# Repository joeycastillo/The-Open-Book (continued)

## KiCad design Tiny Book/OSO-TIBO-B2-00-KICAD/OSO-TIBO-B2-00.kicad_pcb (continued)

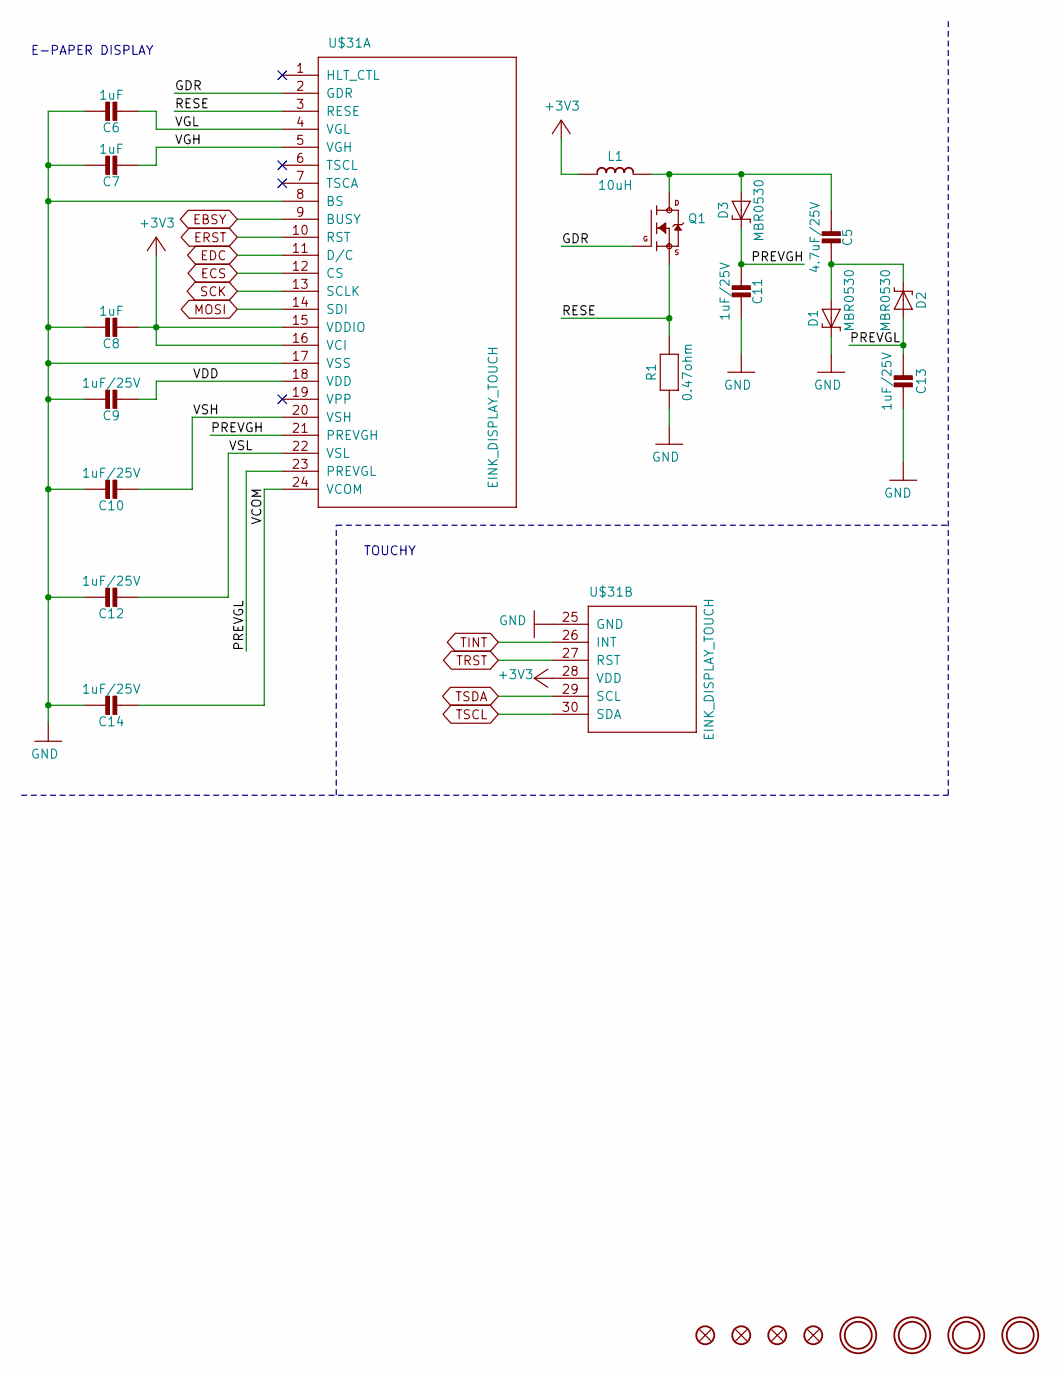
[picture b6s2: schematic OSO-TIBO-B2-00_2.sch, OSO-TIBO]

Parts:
C5: 4.7uF/25V; 0805-NO
C6, C7, C8: 1uF; 0805_10MGAP
C9, C10, C11, C12, C13, C14: 1uF/25V; 0805_10MGAP
D1, D2, D3: MBR0530; SOD-123
FID1, FID2, FID3, FID4: FIDUCIAL_1MM
L1: 10uH; MICROBUILDER_INDUCTOR_4X4MM_NR401_BIGPADS
Q1: IRLML0100; SOT23-3
R1: 0.47ohm; 0805_10MGAP
U$1, U$4, U$5, U$7: MOUNTINGHOLE2.5; MOUNTINGHOLE_2.5_PLATED
U$31: EINK_DISPLAY_TOUCH; EINK_DISPLAY_2_7_IN_TOUCH

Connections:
+3V3: C8.2, L1.P$1 (1), U$31.15 (VDDIO), U$31.16 (VCI), U$31.28 (VDD); also elsewhere on the board
/OSO-TIBO-B2-00_2/GDR: Q1.1 (G), U$31.2 (GDR)
/OSO-TIBO-B2-00_2/PREVGH: C11.1, D3.C, U$31.21 (PREVGH)
/OSO-TIBO-B2-00_2/PREVGL: C13.1, D2.A, U$31.23 (PREVGL)
/OSO-TIBO-B2-00_2/RESE: Q1.2 (S), R1.1, U$31.3 (RESE)
/OSO-TIBO-B2-00_2/VCOM: C14.2, U$31.24 (VCOM)
/OSO-TIBO-B2-00_2/VDD: C9.2, U$31.18 (VDD)
/OSO-TIBO-B2-00_2/VGH: C7.2, U$31.5 (VGH)
/OSO-TIBO-B2-00_2/VGL: C6.2, U$31.4 (VGL)
/OSO-TIBO-B2-00_2/VSH: C10.2, U$31.20 (VSH)
/OSO-TIBO-B2-00_2/VSL: C12.2, U$31.22 (VSL)
EBSY: U$31.9 (BUSY); also elsewhere on the board
ECS: U$31.12 (CS); also elsewhere on the board
EDC: U$31.11 (D/C); also elsewhere on the board
ERST: U$31.10 (RST); also elsewhere on the board
GND: C6.1, C7.1, C8.1, C9.1, C10.1, C11.2, C12.1, C13.2, C14.1, D1.C, R1.2, U$31.8 (BS), U$31.17 (VSS), U$31.25 (GND); also elsewhere on the board
MOSI: U$31.14 (SDI); also elsewhere on the board
unnamed: C5.1, D3.A, L1.P$2 (2), Q1.3 (D)
unnamed: C5.2, D1.A, D2.C
SCK: U$31.13 (SCLK); also elsewhere on the board
TINT: U$31.26 (INT); also elsewhere on the board
TRST: U$31.27 (RST); also elsewhere on the board
TSCL: U$31.30 (SDA); also elsewhere on the board
TSDA: U$31.29 (SCL); also elsewhere on the board

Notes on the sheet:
E-PAPER DISPLAY
TOUCHY

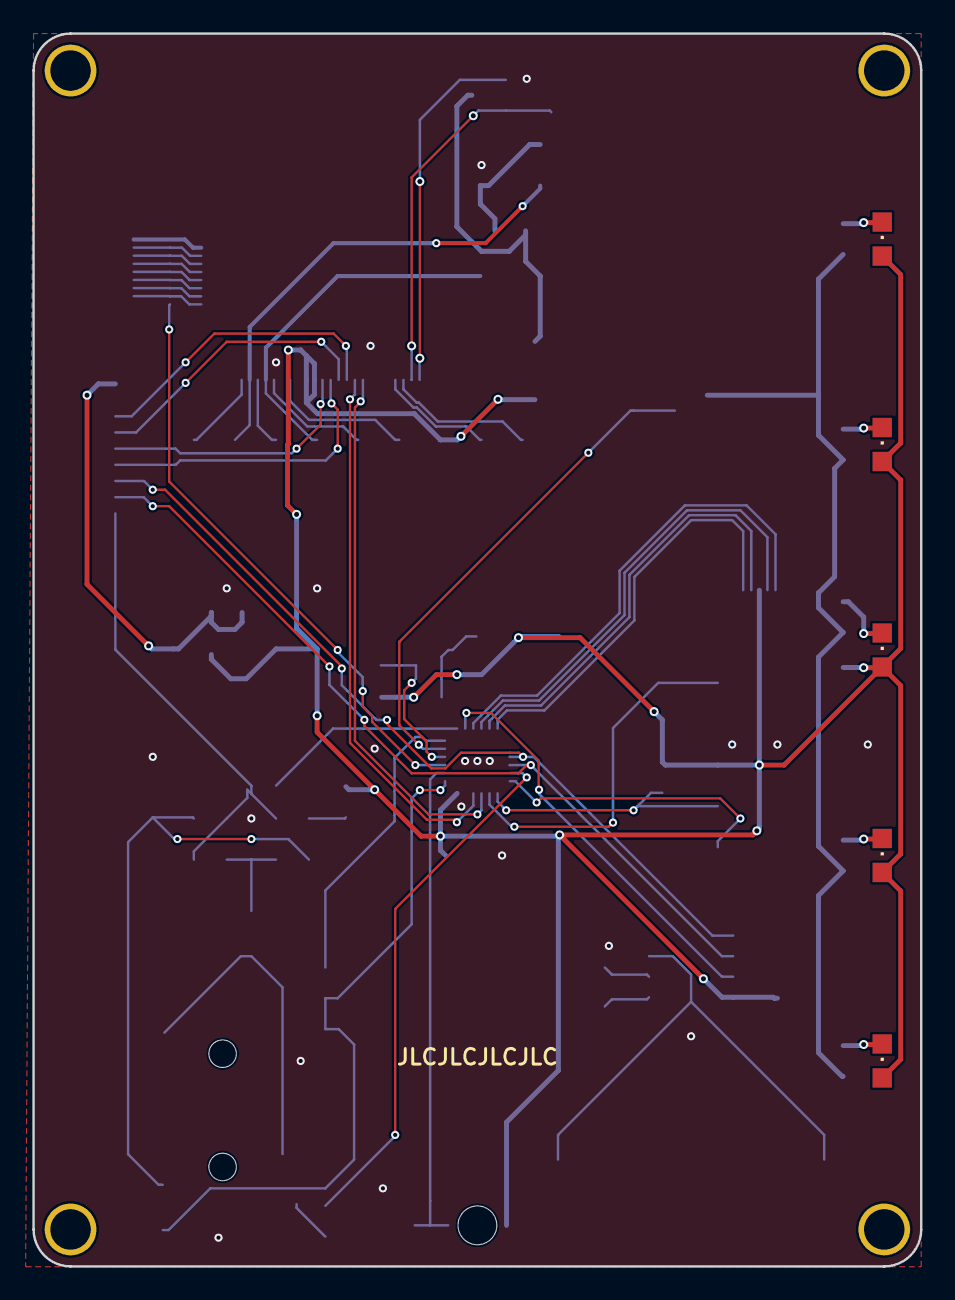
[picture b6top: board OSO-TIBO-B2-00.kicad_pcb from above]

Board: 2 copper layers, 54.9 x 76.2 mm, 78 parts (0 on the bottom side), 62 nets.

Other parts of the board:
LED6: BLU; CHIPLED_0805
U$37: OSO_WORDMARK_THREELINE_450MIL_1000DPI
U$44: OSO_BEAR_250X360MIL_1000DPI

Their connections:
GND: LED6.C; also elsewhere on the board
unnamed 52: LED6.A; also elsewhere on the board

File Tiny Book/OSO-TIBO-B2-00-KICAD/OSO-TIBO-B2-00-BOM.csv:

Reference, Quantity, Value, Footprint, Datasheet
B1 ,1,"CR1220","OSO-TIBO-B2-00:CR1220",""
C1 C17 C2 ,3,"10µF","OSO-TIBO-B2-00:0805-NO",""
C10 C11 C12 C13 C14 C9 ,6,"1uF/25V","OSO-TIBO-B2-00:0805_10MGAP",""
C16 ,1,"100uF","OSO-TIBO-B2-00:C1210",""
C15 C18 C3 ,3,"1uF","OSO-TIBO-B2-00:0805-NO",""
C5 ,1,"4.7uF/25V","OSO-TIBO-B2-00:0805-NO",""
C6 C7 C8 ,3,"1uF","OSO-TIBO-B2-00:0805_10MGAP",""
D1 D2 D3 ,3,"MBR0530","OSO-TIBO-B2-00:SOD-123",""
D6 ,1,"1N4148","OSO-TIBO-B2-00:SOD-123",""
FB1 FB2 ,2,"Ferrite","OSO-TIBO-B2-00:0805",""
FID1 FID2 FID3 FID4 ,4,"FIDUCIAL_1MM","OSO-TIBO-B2-00:FIDUCIAL_1MM",""
J1 ,1,"HEADER-1X9_JSTSH","OSO-TIBO-B2-00:JST_SH9",""
J2 ,1,"SJ-43514-SMT","OSO-TIBO-B2-00:CUI_SJ-43514-SMT",""
J3 ,1,"52746-8","OSO-TIBO-B2-00:52746-8",""
L1 ,1,"10uH","OSO-TIBO-B2-00:MICROBUILDER_INDUCTOR_4X4MM_NR401_BIGPADS",""
LED1 LED2 LED3 LED4 LED5 ,5,"WHITE","OSO-TIBO-B2-00:CHIPLED_0805",""
LED6 ,1,"BLU","OSO-TIBO-B2-00:CHIPLED_0805",""
Q1 ,1,"IRLML0100","OSO-TIBO-B2-00:SOT23-3",""
Q2 ,1,"DMG3406","OSO-TIBO-B2-00:SOT23-WIDE",""
Q3 ,1,"BSS138","OSO-TIBO-B2-00:SOT23-WIDE",""
R1 ,1,"0.47ohm","OSO-TIBO-B2-00:0805_10MGAP",""
R11 ,1,"10K","OSO-TIBO-B2-00:EXB2HV",""
R13 R14 R15 R16 R17 ,5,"10Ω","OSO-TIBO-B2-00:0805-NO",""
R10 R12 R18 R2 R4 R9 ,6,"10K","OSO-TIBO-B2-00:0805-NO",""
R3 ,1,"100~~220 (TBD)","OSO-TIBO-B2-00:0805-NO",""
R5 R6 ,2,"10K","OSO-TIBO-B2-00:_0805MP",""
R7 R8 ,2,"100","OSO-TIBO-B2-00:_0805MP",""
SJ1 ,1,"SOLDERJUMPERREFLOW_NOPASTE","OSO-TIBO-B2-00:SOLDERJUMPER_REFLOW_NOPASTE",""
SP2 ,1,"7.5mm SPK","OSO-TIBO-B2-00:BUZZER_SMT_5MM",""
TP1 TP2 TP3 TP4 TP5 ,5,"TESTPOINTROUND2MMNO","OSO-TIBO-B2-00:TESTPOINT_ROUND_2MM_NO",""
U$1 U$4 U$5 U$7 ,4,"MOUNTINGHOLE2.5","OSO-TIBO-B2-00:MOUNTINGHOLE_2.5_PLATED",""
U$31 ,1,"EINK_DISPLAY_TOUCH","OSO-TIBO-B2-00:EINK_DISPLAY_2_7_IN_TOUCH",""
U1 ,1,"AP2112-3.3","OSO-TIBO-B2-00:SOT23-5",""
U2 ,1,"ATSAMD09D14A-MU","OSO-TIBO-B2-00:QFN24_4MM",""
U3 ,1,"ALS-PT21","OSO-TIBO-B2-00:ALS-PT26-21C",""
U4 ,1,"PCF8523T","OSO-TIBO-B2-00:SOIC8_150MIL",""
X1 ,1,"32768 Hz/CL=7pF","OSO-TIBO-B2-00:XTAL3215",""

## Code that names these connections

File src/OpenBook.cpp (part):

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 @brief Configures the e-ink screen.
 @param srcs Chip select pin for the SRAM. Pass in OPENBOOK_NOT_PRESENT if you
             have omitted this chip.
 @param ecs Chip select pin for the e-ink screen.
 @param edc Data/command pin for the e-ink screen.
 @param erst Reset pin for the e-ink screen.
 @param ebsy Busy pin for the e-ink screen.
 @param spi Address of the SPI bus for the screen and SRAM chip.
 @param width Native width of the display
 @param height Native height of the display
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 @param clock Clock pin for the shift register
 @returns true as long as you passed in valid pins.
 @note This is currently the button solution for the Open Book. The Lock button
       is NOT on the shift register, though; it's on a SAMD51 interrupt pin, and
       SD Card Detect is on the shift register. This feels very inelegant and I
       may rework this in the final revision.
*/
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
/**
 @brief Configures the buttons for devices with a MCP23008 I2C port expander.
 @param interrupt The port expander's interrupt pin.
 @returns always returns true for now
 @note This is currently the button solution for the wing. All buttons are on
       the port expander, including the Lock button.
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    this->ioExpander = ioExpander;

    if (interrupt >= 0) {
        pinMode(interrupt, INPUT);
    }
    this->activeState = active;
    this->buttonInterrupt = interrupt;
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}

/**
 @brief Configures pins for audio input and output.
 @param left DAC pin for the left or mono channel.
 @param right DAC pin for the right channel, or OPENBOOK_NOT_PRESENT if using
              the wing where audio output is mono.
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                     breakout board into a STEMMA port, and get amplified mic
                     input that way; pass in A1 or A2, depending on the port you
                     are using.
 @returns true as long as at least one audio pin was configured.
*/
bool OpenBook::configureAudio(int8_t left, int8_t right, int8_t inlineMic, int8_t amplifiedMic) {
    int8_t channels = 0;
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
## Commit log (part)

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2019-08-14 remove 5V option, more complicated than I thought
2019-08-16 final commit of rev B as submitted to OSH Park
2019-08-16 add demo code from show and tell
2019-09-02 final tweaks and BOM for rev B
2019-09-03 added a rev C, embiggens the board at top
2019-09-09 eink display's tDocu layer was off, scooting it back into line with reality
2019-09-11 update readme with state of the project and goals
2019-09-13 lol nevermind this thru-hole switch is cheaper
2019-09-15 WIP samd51 ebook
2019-09-16 move traces out of text areas
2019-09-16 also tent power vias
2019-09-16 more documentation tweaks
2019-09-16 more label tweaks
2019-09-20 add logos and such
2019-09-23 wire FCS to M4's 'extra' pin
2019-09-24 move leds topside, thru-hole style. other design tweaks
2019-10-10 Digikey Bill of Materials
    Excludes e-ink panel from buyepaper.com
    Excludes microSD socket and SMT headers from Adafruit
    Includes Adafruit M4 Feather from Digikey
2019-10-10 Now includes MicroSD Socket from Digikey
    Excludes e-ink panel from buyepaper.com
    Excludes SMT headers from Adafruit
    Includes Adafruit M4 Feather from Digikey
    Includes MicroSD Socket from Digikey (instead of Adafruit)
2019-10-14 Make compatible with kitspace.org
2019-10-15 add these cool right-angle LEDs (that i ordered too many of)
2019-10-15 move surface mount chip away from thru-hole components
2019-10-16 last minute tweaks to text and arrangement
2019-10-17 yet more last minute text tweaks
2019-10-17 minor footprint and label tweaks
2019-10-17 final version of open book A1-01 submitted to OSH Park
2019-10-27 wip rev 2 with lessons learned
2019-10-29 rearrange power supply block, power neopixel from regulator
2019-10-29 fix buttons, add pulldown resistors & remove lock btn from shift reg
2019-10-29 silkscreen adjustments to ebook wing rev 3
2019-11-01 put sd card detect signal on shift register
2019-11-01 make the FCS jumper open by default
2019-11-04 route card detect signal
2019-11-04 improved silkscreen documentation
2019-11-04 scoot filter caps away from chip (easier for manual rework if needed)
2019-11-04 tweak documentation of QSPI flash
2019-11-05 more silkscreen tweaks
2019-11-05 renumber passives, update silkscreen
2019-11-05 improve clearance around C24
2019-11-05 draw outline around led
2019-11-05 correct component values
2019-11-05 remove wire stub
2019-11-06 add documentation to front side
2019-11-06 move SWCLK pullup to microcontroller block
2019-11-06 scoot swd connector up a bit
2019-11-07 fix typo
2019-11-07 more clearance around resistor arrays
2019-11-08 tweaks to front documentation
2019-11-08 restore reset stability circuit
2019-11-09 note LED pin on silkscreen
2019-11-09 tweak button labels
2019-11-09 make neopixel notes match other notes
2019-11-09 space out mic amp section for easier manual placement
2019-11-09 add OSHPark to colophon
2019-11-09 scoot OSO logo down
2019-11-09 final version of open book A1-02 submitted to OSH Park
2019-11-09 restore calvino quote, final version of wing A1-03 submitted to OSH Park
2019-11-10 add example sketch to test screen
2019-11-10 update readme with new photos
2019-11-12 add BOM to readme
2019-11-24 add mailing list signup link
2019-11-27 wip: open book arduino library
2019-11-28 update screen test to use open book arduino lib
2019-11-29 WIP custom driver for IL0398 e-ink controller
2019-11-30 invert busy logic to match panel spec
2019-11-30 typo on the silkscreen, correct pin numbers for button register
2019-11-30 clear shift register when setting up
2019-12-01 WIP open book rev 3?
2019-12-01 add indicator LED for full charge
2019-12-01 update quotes demo to use babel's word wrapping feature
2019-12-01 handle button active state as property, not macro
2019-12-02 partial update looks good
2019-12-03 set rotation in OpenBook, not display driver
2019-12-03 add board readme, mark rev 03 as WIP
2019-12-03 maybe power and gnd pads shouldn't be so close together
2019-12-06 starting over with next rev
2019-12-06 start rev 4, remove SRAM
2019-12-06 use max4468 for mic amp shutdown capability
2019-12-06 rev 3 (not made) just fixes a silkscreen typo
2019-12-06 rev 4: move babel chip into SRAM spot
2019-12-06 resistor array to monitor both VBAT and VBUS
2019-12-06 route A11/VBUSMON
2019-12-06 add green led for full battery
2019-12-06 fix typo in net name
2019-12-09 prettify voltage monitors in schematic
2019-12-10 readme tweak
2019-12-10 rename capacitors around samd51
2019-12-10 update 'building your board' silkscreen
2019-12-13 heart of darkness demo + voice commands
2019-12-26 more work on partial refresh
2019-12-27 new pin definitions for rev 4
2019-12-30 update README, main board image
2020-01-12 no need to resend waveforms; faster partial refresh
2020-01-14 this was a silly typo
2020-01-15 expose sd card as usb mass storage device
2020-01-20 let sketches decide how they want to use SD and flash
2020-01-20 add tiny book M4 board
2020-01-23 update README, board image
2020-01-25 better thru-hole button footprints, new right angle buttons
2020-01-25 connect shield to ground via RC (reduce headphone noise?)
2020-01-25 schematic cleanup
2020-01-25 right angle neopixel near reset button
2020-01-25 fix silksreen typo (serial is SERCOM5)
2020-01-25 DNP side buttons
2020-01-25 update README with rev 5 notes, add schematics
2020-01-25 WIP wing rev 5 with new buttons
2020-01-25 wing: new footprint for inductor
2020-01-25 fix new button labels
2020-01-25 rename alt buttons DNP
2020-01-25 wing: update to higher res OSO artwork
2020-01-28 if i do this again, accessory should be on PA05 to make use of the DAC
2020-01-28 swapped micraw and accessoory pins, need to route signals
2020-01-28 silkscreen and dimension tweaks
2020-01-28 surface mount reset button
2020-01-28 route accessory and mic raw signals
2020-01-28 use 4MB flash so babel can live there
2020-01-28 fix I2C routing snafu
2020-01-28 bump revision
2020-02-12 Add an OSH Park Link
    I had to dig on oshpark's sharing functionality to find the current rev of the board. It would be nice to link it from the README
2020-02-13 silkscreen updates to e-book wing
2020-02-13 rev 5 of the wing
2020-02-25 update BOM for wing rev 5
2020-03-03 [README] table headers copied at the end of table
    To help with readability since the table is quite long (avoid scrolling up / down to check which column is which)
2020-05-24 disable SRAM on feather M4
2020-05-24 MVBook update for e-book wing
2020-05-24 add sample books for MVBook
2020-06-05 last tweaks to A1-05 before sending to fab
2020-06-12 update BOM and gerbers for final rev of wing
2020-06-23 add method for getting sd card state
2020-06-23 fix audio channels
2020-06-23 add sketch to burn Open Book bootloader
2020-06-23 add pin definition for neopixel
2020-06-23 add open book system test sketch
2020-06-23 Buttons & SD card change
2020-06-24 rename example sketch
2020-06-25 last minute tweaks to system test
2020-06-27 document SD card detect method
2020-06-27 fix audio pin modes
2020-06-27 june README update, rev 5 board photos
2020-06-27 add hackaday.io link to readme
2020-07-04 remove old PCB design files
2020-07-07 update readme and BOM for kitspace
2020-07-07 update open book board notes
2020-07-07 include README.md in Kitspace pages
    We don't currently pick this up automatically for multi projects. You can point it at another readme if you have a board-specific one.
2020-07-07 add documentation printouts for both boards
2020-07-15 add C2 to e-book wing BOM
2020-07-16 fix R12 reference in the BOM
2020-07-20 e-book wing: fix one un-tented via
2020-08-13 tiny book!
2020-08-16 IL0398 driver: fix shades of gray
2020-08-17 add driver for IL91874 with grayscale mode
2020-08-21 no need to include these constants, already defined
2020-08-21 partial and quick modes for IL91874
2020-08-22 replace digireel part numbers with cut tape
2020-08-23 update BOM in documentation packet
2020-08-24 update wing setup guide
2020-08-28 add tiny book circuitpython board definition
2020-08-30 BOM links on kitspace were the wrong way round
    Link for featherwing took you to open book feather and vice versa. corrected, no other changes made.
2020-08-30 update materials for e-book wing A1-06
2020-08-30 use better microSD card slot
2020-09-13 book rev 6: pull-ups on SPI devices, headphone bias
2020-09-13 rotate OSO logo to match open book
2020-09-13 add gerbers for latest order
2020-10-01 move drill files to gerbers folder (#37)
2020-10-10 Open Book PCB Migration to KiCad
    This is a set of KiCad files from the posted Eagle files.
    For this conversion, the latest version Eagle files were used (OSO-BOOK-A1-06).
    The schematics were imported in three sheets, plus the cover sheet (total four).
    All text, net labels, global net labels, component values and references were adjusted to KiCad’s default size for consistency.
    Some nets were imported with net labels (because they were present only on one sheet) and some with global net labels (because they were used in multiple sheets).
    All duplicate global net labels were deleted from power nets (power nets are global nets by default).
2020-10-10 BTN_LOCK1 silkscreen location adjustment
2020-10-11 E-Book Feather Wing PCB Migration to KiCad
    This is a set of KiCad files from the posted Eagle files.
    For this conversion, the latest version Eagle files were used (OSO-BOWI-A1-06).
    The schematic was imported in a single sheet.
    All text, net labels, global net labels, component values and references were adjusted to KiCad’s default size for consistency.
    All duplicate global net labels were deleted from power nets (power nets are global nets by default).
    The converted libraries (symbol and footprints) were examined for accuracy.
2020-10-11 Tiny Book (OSO-TIBO-B2-00) Migration to KiCad
2020-10-13 add circuitpython EPD drivers
2020-10-14 Revised E-Book Wing silkscreen labels.
    Addressing comment for the solder jumpers on the E-Book Wing that had silkscreen labels, such as TX1/RX1/ECS1 etc, where the number 1 was appended after the original name, which was crowding the labe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
2020-10-19 add link to e-book wing assembly video
2020-10-29 fix mic preamp glitch in system test
2020-10-30 experiment for use with textformat branch of babel
2020-10-30 add documentation for BOOK A1 rev 06
2020-10-30 point kitspace to revision 06 of book
2020-10-30 add 3D models of book and wing
2020-10-30 update readme and schematics
2020-10-30 add acknowledgements for 3d models
2020-10-30 fix small typo in readme
2020-10-30 add render images / rename for consistency
2020-11-01 1-click BOM: fix typo
2020-11-01 MVBook: support multi-page menu
2020-11-01 store user's place in book
2020-11-01 update roadmap in README
2020-11-03 MVBook: add screen lock, splash screen at boot
2020-11-03 MVBook: improve menu system responsiveness
2020-12-01 first crack at ESP32-S2 Open Book
2020-12-04 Update open-book-printout.md
    Fix broken(?) link to Arduino library manager URL
2020-12-12 examples: add shebang to bookbinder.py (fixes #45)
2020-12-16 fix incorrect part number in e-book wing BOM
2020-12-22 Alternative parts for ESP32-S2 version
    - changed USB-C connector (https://lcsc.com/product-detail/USB-Type-C_Korean-Hroparts-Elec-TYPE-C-31-M-12_C165948.html)
    - changed uSD card slot (https://www.aliexpress.com/item/32763208642.html)
    - added cutout for ESP32-S2 PCB antena
2020-12-22 Revert "Buttons & SD card change"
    This reverts commit 564ec3b5048e0d7899cd32f6cb14d9a07736022d.
2021-06-06 open book abridged with castellated EPD driver
2022-07-22 Fix word order typo.
    s/some stopped/stopped some/
2022-09-28 project reboot
2022-09-28 add pi pico book, new castellated module
2022-09-28 add note on where to find firmware
2022-09-28 fix link
2022-09-28 typo
2022-11-09 add 3d printed case design
2022-11-15 rev 5: remove zener diodes, silkscreen tweaks
2022-11-15 shrink outline of JLC module, size minimum no longer applies
2022-11-15 add kistpace files
2022-11-19 docs: Adds License to readme
    Would resolve https://github.com/joeycastillo/The-Open-Book/issues/63 if merged
2022-11-29 update JLC fabrication files
2022-12-07 Update documentation links (fixes #66)
2022-12-16 Fix capacitor part number
2023-07-03 convert castellated e-paper driver project to KiCAD
2023-07-21 ESP32-S3 book, rev 0 fabricated july 2023
2023-08-30 rev 06
2023-08-30 add EN pullup to ESP32-S3 book
